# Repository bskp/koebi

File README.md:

Köbi: Robotic Puppeteering
==========================

Köbi is a 6-channel wireless stepper controller consisting of a [SparkFun ESP32 Thing](https://www.sparkfun.com/products/13907) (red) and a **breakout shield** (white). The latter is inspired by [RAMPS](https://reprap.org/wiki/Arduino_Mega_Pololu_Shield) and accomodates six stepper motor drivers ([TMC2130 StepSticks](https://shop.watterott.com/SilentStepStick-TMC2130), green), optical endstop sensors and fan control.

The software on the ESP32 provides an [OSC (Open Sound Control)](https://en.wikipedia.org/wiki/Open_Sound_Control) server. This, in combination with a matching tablet GUI for the modular [TouchOSC](https://hexler.net/products/touchosc) app allows easy control of the steppers (which are the six thread spools).

Alternatively, the module can be controlled by any other OSC client. The OSC endpoints are documented at the [end of this page](#osc-api).

Features
--------

- 500g per thread
- Velocities up to 2m/s
- Wireless control
- Sub-centimeter precision
- (Almost) unlimited thread lengths
- Position and speed feedback for every channel
- Self-calibration using optical markers on the threads (TODO)
- Motor drivers configured using SPI, allowing for:
    - Microstepping reconfiguration (during operation)
    - Current control
    - Load estimation (TODO)
    - Count of missed steps if overload occurs (TODO)
- Easily extendable code written in [Micropython](https://micropython.org)
- Wireless console (WEBREPL) and code update (FTP)
- Additional I2C / SPI / GPIOs broken out

There are a ton of things you can hook it to. Feel free to reuse!

Software + Firmware
-------------------

The ESP32-Board runs a **special build** of the Micropython firmware due to two requirements:

- The PWM hardware module, which generates the **pulses for the  stepper motors**, is currently not supported by Micropython. This special build includes a Python module supporting it, implemented in C: The [MCPWM](https://github.com/bskp/micropython_esp32_mcpwm) module.

- The Python module for the **Trinamic TMC steppper drivers** (which holds names and descriptions to dozens of its registers) had to be frozen in order to save memory: The [TMC]() module. (TODO: Not published yet)

How much do you need? To get you started with the software, each of this three guides covers a different level:
1. **[Getting started](getting_started.md)**: Setup and interact with Köbi _using a tablet_ and the default OSC API
2. **[Hacking](hacking.md)**: Extend Köbis functionality _by modifying the Micropython_ code running the ESP32
3. **[Developing](developing.md)**: Modify the _Micropython firmware (written in C)_ to improve on the modules [MCPWM]() or [TMC](). These are part of the modified Micropython built, ie. "frozen"

Hardware
--------

This repo also supplies you with everything needed to build your own Köbi.

### Bill of Ordering Materials

| Thing                 | Brand    | Part      | Source          | Price |
|-----------------------|----------|-----------|-----------------|-------|
| Steppers (5-pack)     | Hanpose  | 17HS4401  | AliExpress      | 38.-  |
| Voltage Supply (120W) | GYU&PW   | S-120-24  | AliExpress      | 13.-  |
| ESP32 Thing           | SparkFun | DEV-13907 | [bastelgarage](https://www.bastelgarage.ch/sparkfun-esp32-thing) | 22.- |

SN74LS138N

- bom: steppers, supply, esp32, tmcs, pcb/components, wall plug

### 3D Printed Parts

**Thread Spool (40mm)**: [.stl](parts/Sp40A.stl)

- stl, link zu onshape

### Printed Circuit Board
- PCB-Daten als pdf, gerber und kicad.

Ideas
-----

- [x] Coordinated 2-axis movements
- [ ] Load visualization
- [ ] Presets with persistent storage
- [ ] Self-calibration with markers
- [x] Sequencer (Sine and jitter movements)
- [x] Coordinated movements for more than 2 axes
- [ ] Inverse kinematics

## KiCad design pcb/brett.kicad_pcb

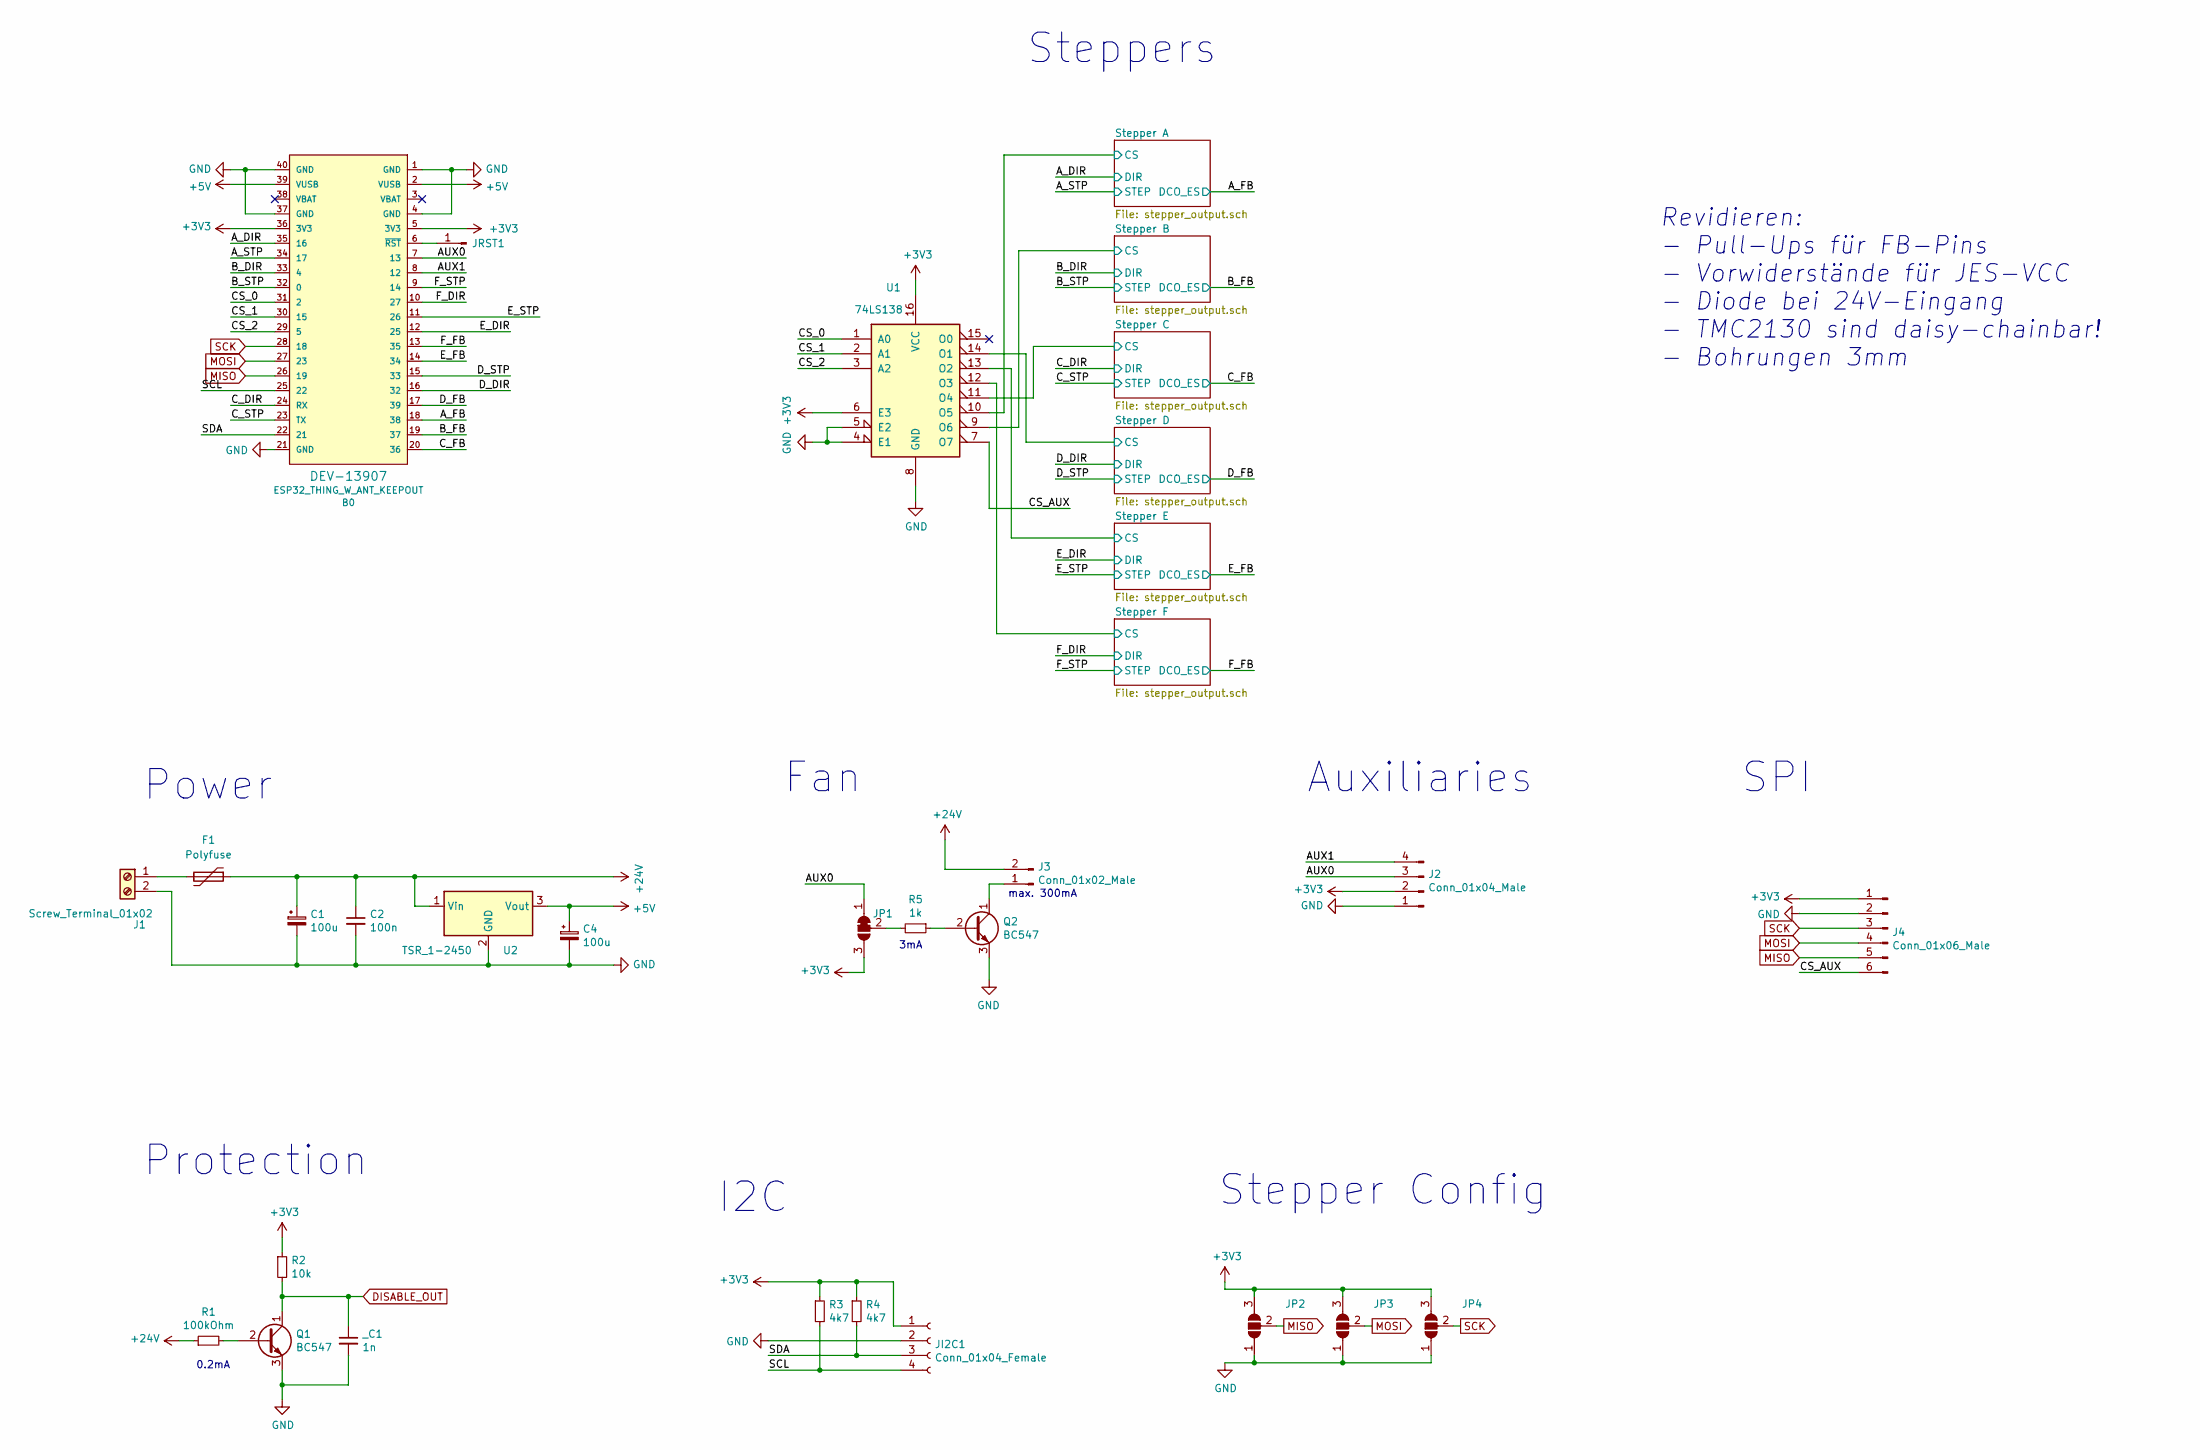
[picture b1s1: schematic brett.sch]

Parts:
B0: ESP32_THING_W_ANT_KEEPOUT; ESP32_THING
C1, C4: 100u; CP_Radial_D8.0mm_P3.50mm
C2: 100n; C_Radial_D6.3mm_H5.0mm_P2.50mm
F1: Polyfuse; Fuse_Bourns_MF-RHT1000
J1: Screw_Terminal_01x02; TerminalBlock_RND_205-00232_1x02_P5.08mm_Horizontal
J2: Conn_01x04_Male; PinHeader_1x04_P2.54mm_Vertical
J3: Conn_01x02_Male; PinHeader_1x02_P2.54mm_Vertical
J4: Conn_01x06_Male; PinHeader_1x06_P2.54mm_Vertical
JI2C1: Conn_01x04_Female; PinHeader_1x04_P2.54mm_Vertical
JP1: SolderJumper_3_Bridged12; SolderJumper-3_P1.3mm_Bridged12_RoundedPad1.0x1.5mm
JP2, JP3, JP4: SolderJumper_3_Open; SolderJumper-3_P1.3mm_Open_RoundedPad1.0x1.5mm
JRST1: Conn_01x01_Male; PinHeader_1x01_P2.54mm_Vertical
Q1, Q2: BC547; TO-92_Inline
R1: 100kOhm; R_Axial_DIN0207_L6.3mm_D2.5mm_P7.62mm_Horizontal
R2: 10k; R_Axial_DIN0207_L6.3mm_D2.5mm_P7.62mm_Horizontal
R3, R4: 4k7; R_Axial_DIN0207_L6.3mm_D2.5mm_P7.62mm_Horizontal
R5: 1k; R_Axial_DIN0207_L6.3mm_D2.5mm_P7.62mm_Horizontal
U1: 74LS138; DIP-16_W7.62mm
U2: TSR_1-2450; Converter_DCDC_TRACO_TSR-1_THT
_C1: 1n; C_Radial_D6.3mm_H5.0mm_P2.50mm

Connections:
+5V: B0.2 (VUSB), B0.39 (VUSB), C4.1, U2.3 (Vout)
+24V: C1.1, C2.1, F1.1, J3.2, R1.1, U2.1 (Vin); also elsewhere on the board
/AUX0: B0.7 (13), J2.3, JP1.1 (A); also elsewhere on the board
/AUX1: B0.8 (12), J2.4; also elsewhere on the board
/A_DIR: B0.35 (16); also elsewhere on the board
/A_FB: B0.18 (38); also elsewhere on the board
/A_STP: B0.34 (17); also elsewhere on the board
/B_DIR: B0.33 (4); also elsewhere on the board
/B_FB: B0.19 (37); also elsewhere on the board
/B_STP: B0.32 (0); also elsewhere on the board
/CS_0: B0.31 (2), U1.1 (A0)
/CS_1: B0.30 (15), U1.2 (A1)
/CS_2: B0.29 (5), U1.3 (A2)
/CS_AUX: J4.6, U1.7 (O7); also elsewhere on the board
/C_DIR: B0.24 (RX); also elsewhere on the board
/C_FB: B0.20 (36); also elsewhere on the board
/C_STP: B0.23 (TX); also elsewhere on the board
/D_DIR: B0.16 (32); also elsewhere on the board
/D_FB: B0.17 (39); also elsewhere on the board
/D_STP: B0.15 (33); also elsewhere on the board
/E_DIR: B0.12 (25); also elsewhere on the board
/E_FB: B0.14 (34); also elsewhere on the board
/E_STP: B0.11 (26); also elsewhere on the board
/F_DIR: B0.10 (27); also elsewhere on the board
/F_FB: B0.13 (35); also elsewhere on the board
/F_STP: B0.9 (14); also elsewhere on the board
/SCL: B0.25 (22), JI2C1.4, R3.2
/SDA: B0.22 (21), JI2C1.3, R4.2
/Stepper A/CS: U1.10 (O5); also elsewhere on the board
/Stepper B/CS: U1.9 (O6); also elsewhere on the board
/Stepper C/CS: U1.11 (O4); also elsewhere on the board
/Stepper D/CS: U1.14 (O1); also elsewhere on the board
/Stepper E/CS: U1.13 (O2); also elsewhere on the board
/Stepper F/CS: U1.12 (O3); also elsewhere on the board
DISABLE_OUT: Q1.1 (C), R2.2, _C1.1; also elsewhere on the board
MISO: B0.26 (19), J4.5, JP2.2 (C); also elsewhere on the board
MOSI: B0.27 (23), J4.4, JP3.2 (C); also elsewhere on the board
unnamed: B0.6 (~RST~), JRST1.1
unnamed: F1.2, J1.1
unnamed: J3.1, Q2.1 (C)
unnamed: JP1.2 (C), R5.2
unnamed: Q1.2 (B), R1.2
unnamed: Q2.2 (B), R5.1
SCK: B0.28 (18), J4.3, JP4.2 (C); also elsewhere on the board

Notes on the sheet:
Stepper Config
Power
I2C
Protection
Fan
3mA
max. 300mA
Auxiliaries
0.2mA
Steppers
SPI
Revidieren: - Pull-Ups für FB-Pins - Vorwiderstände für JES-VCC - Diode bei 24V-Eingang - TMC2130 sind daisy-chainbar! - Bohrungen 3mm

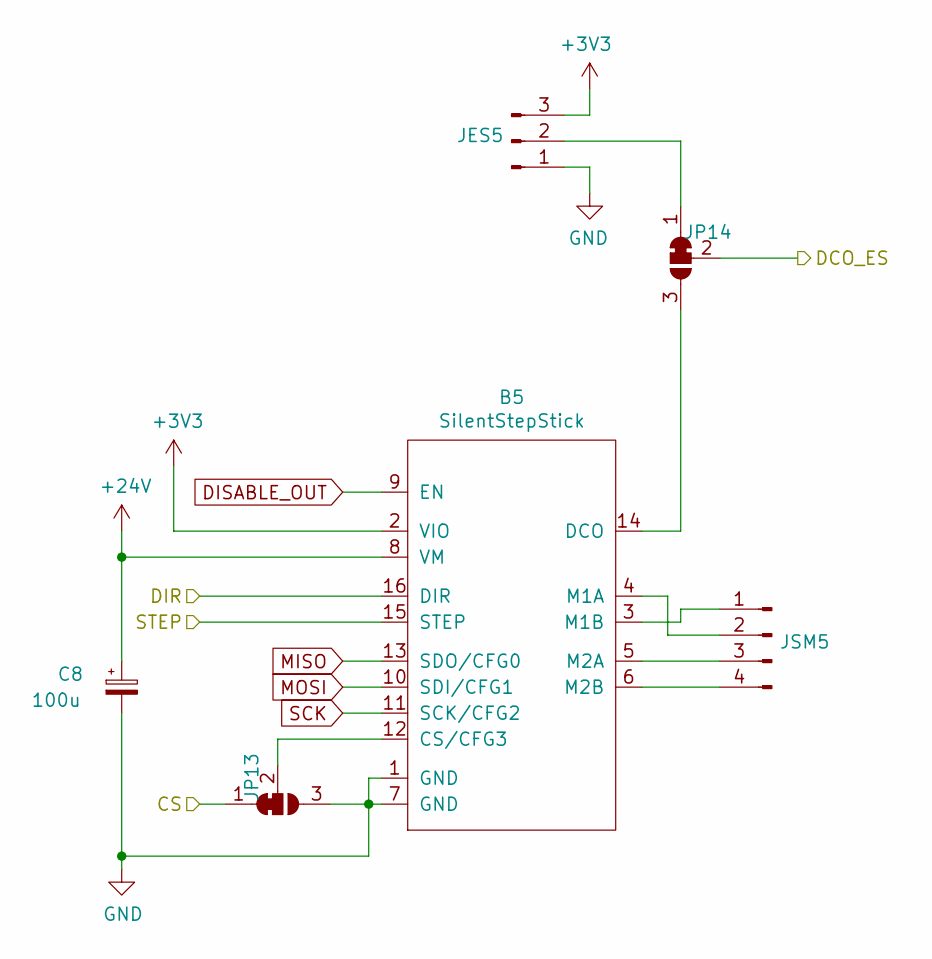
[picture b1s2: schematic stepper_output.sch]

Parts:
B1: SilentStepStick; StepStick
C3: 100u; CP_Radial_D8.0mm_P3.50mm
JES1: Conn_01x03_Male; PinHeader_1x03_P2.54mm_Vertical
JP8, JP9: SolderJumper_3_Bridged12; SolderJumper-3_P1.3mm_Bridged12_RoundedPad1.0x1.5mm
JSM1: Conn_01x04_Male; PinHeader_1x04_P2.54mm_Vertical

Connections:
+24V: B1.8 (VM), C3.1; also elsewhere on the board
/A_DIR: B1.16 (DIR); also elsewhere on the board
/A_FB: JP9.2 (C); also elsewhere on the board
/A_STP: B1.15 (STEP); also elsewhere on the board
/Stepper A/CS: JP8.1 (A); also elsewhere on the board
DISABLE_OUT: B1.9 (EN); also elsewhere on the board
MISO: B1.13 (SDO/CFG0); also elsewhere on the board
MOSI: B1.10 (SDI/CFG1); also elsewhere on the board
unnamed: B1.3 (M1B), JSM1.1
unnamed: B1.4 (M1A), JSM1.2
unnamed: B1.5 (M2A), JSM1.3
unnamed: B1.6 (M2B), JSM1.4
unnamed: B1.12 (CS/CFG3), JP8.2 (C)
unnamed: B1.14 (DCO), JP9.3 (B)
unnamed: JES1.2, JP9.1 (A)
SCK: B1.11 (SCK/CFG2); also elsewhere on the board

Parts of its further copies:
B2, B3, B4, B5, B6: SilentStepStick; StepStick
C5, C6, C7, C8, C9: 100u; CP_Radial_D8.0mm_P3.50mm
J5: Conn_01x03_Male; PinHeader_1x03_P2.54mm_Vertical
J6: Conn_01x04_Male; PinHeader_1x04_P2.54mm_Vertical
JES2, JES3, JES4, JES5, JES6: Conn_01x03_Male; PinHeader_1x03_P2.54mm_Vertical
JP5, JP6, JP7, JP10, JP11, JP12, JP13, JP14, JP15, JP16: SolderJumper_3_Bridged12; SolderJumper-3_P1.3mm_Bridged12_RoundedPad1.0x1.5mm
JSM2, JSM3, JSM4, JSM5, JSM6: Conn_01x04_Male; PinHeader_1x04_P2.54mm_Vertical

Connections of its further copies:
+24V: B2.8 (VM), B3.8 (VM), B4.8 (VM), B5.8 (VM), B6.8 (VM), C5.1, C6.1, C7.1, C8.1, C9.1; also elsewhere on the board
/B_DIR: B2.16 (DIR); also elsewhere on the board
/B_FB: JP6.2 (C); also elsewhere on the board
/B_STP: B2.15 (STEP); also elsewhere on the board
/C_DIR: B3.16 (DIR); also elsewhere on the board
/C_FB: JP10.2 (C); also elsewhere on the board
/C_STP: B3.15 (STEP); also elsewhere on the board
/D_DIR: B4.16 (DIR); also elsewhere on the board
/D_FB: JP12.2 (C); also elsewhere on the board
/D_STP: B4.15 (STEP); also elsewhere on the board
/E_DIR: B5.16 (DIR); also elsewhere on the board
/E_FB: JP14.2 (C); also elsewhere on the board
/E_STP: B5.15 (STEP); also elsewhere on the board
/F_DIR: B6.16 (DIR); also elsewhere on the board
/F_FB: JP16.2 (C); also elsewhere on the board
/F_STP: B6.15 (STEP); also elsewhere on the board
/Stepper B/CS: JP5.1 (A); also elsewhere on the board
/Stepper C/CS: JP7.1 (A); also elsewhere on the board
/Stepper D/CS: JP11.1 (A); also elsewhere on the board
/Stepper E/CS: JP13.1 (A); also elsewhere on the board
/Stepper F/CS: JP15.1 (A); also elsewhere on the board
DISABLE_OUT: B2.9 (EN), B3.9 (EN), B4.9 (EN), B5.9 (EN), B6.9 (EN); also elsewhere on the board
MISO: B2.13 (SDO/CFG0), B3.13 (SDO/CFG0), B4.13 (SDO/CFG0), B5.13 (SDO/CFG0), B6.13 (SDO/CFG0); also elsewhere on the board
MOSI: B2.10 (SDI/CFG1), B3.10 (SDI/CFG1), B4.10 (SDI/CFG1), B5.10 (SDI/CFG1), B6.10 (SDI/CFG1); also elsewhere on the board
unnamed: B2.3 (M1B), JSM2.1
unnamed: B2.4 (M1A), JSM2.2
unnamed: B2.5 (M2A), JSM2.3
unnamed: B2.6 (M2B), JSM2.4
unnamed: B2.12 (CS/CFG3), JP5.2 (C)
unnamed: B2.14 (DCO), JP6.3 (B)
unnamed: B3.3 (M1B), JSM3.1
unnamed: B3.4 (M1A), JSM3.2
unnamed: B3.5 (M2A), JSM3.3
unnamed: B3.6 (M2B), JSM3.4
unnamed: B3.12 (CS/CFG3), JP7.2 (C)
unnamed: B3.14 (DCO), JP10.3 (B)
unnamed: B4.3 (M1B), JSM4.1
unnamed: B4.4 (M1A), JSM4.2
unnamed: B4.5 (M2A), JSM4.3
unnamed: B4.6 (M2B), JSM4.4
unnamed: B4.12 (CS/CFG3), JP11.2 (C)
unnamed: B4.14 (DCO), JP12.3 (B)
unnamed: B5.3 (M1B), JSM5.1
unnamed: B5.4 (M1A), JSM5.2
unnamed: B5.5 (M2A), JSM5.3
unnamed: B5.6 (M2B), JSM5.4
unnamed: B5.12 (CS/CFG3), JP13.2 (C)
unnamed: B5.14 (DCO), JP14.3 (B)
unnamed: B6.3 (M1B), JSM6.1
unnamed: B6.4 (M1A), JSM6.2
unnamed: B6.5 (M2A), JSM6.3
unnamed: B6.6 (M2B), JSM6.4
unnamed: B6.12 (CS/CFG3), JP15.2 (C)
unnamed: B6.14 (DCO), JP16.3 (B)
unnamed: JES2.2, JP6.1 (A)
unnamed: JES3.2, JP10.1 (A)
unnamed: JES4.2, JP12.1 (A)
unnamed: JES5.2, JP14.1 (A)
unnamed: JES6.2, JP16.1 (A)
SCK: B2.11 (SCK/CFG2), B3.11 (SCK/CFG2), B4.11 (SCK/CFG2), B5.11 (SCK/CFG2), B6.11 (SCK/CFG2); also elsewhere on the board

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
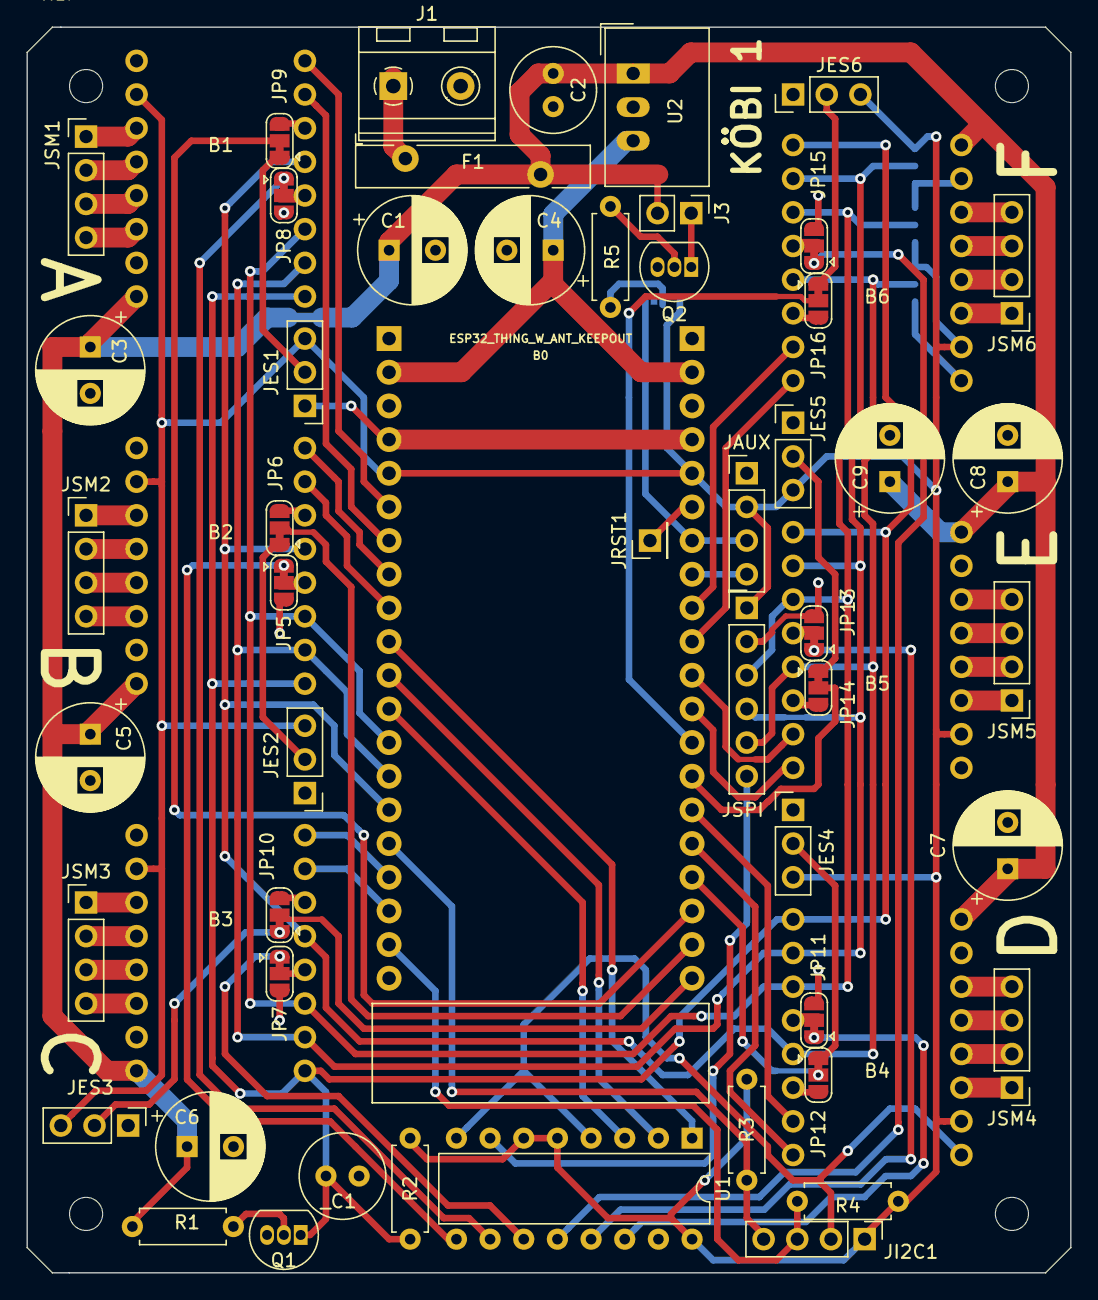
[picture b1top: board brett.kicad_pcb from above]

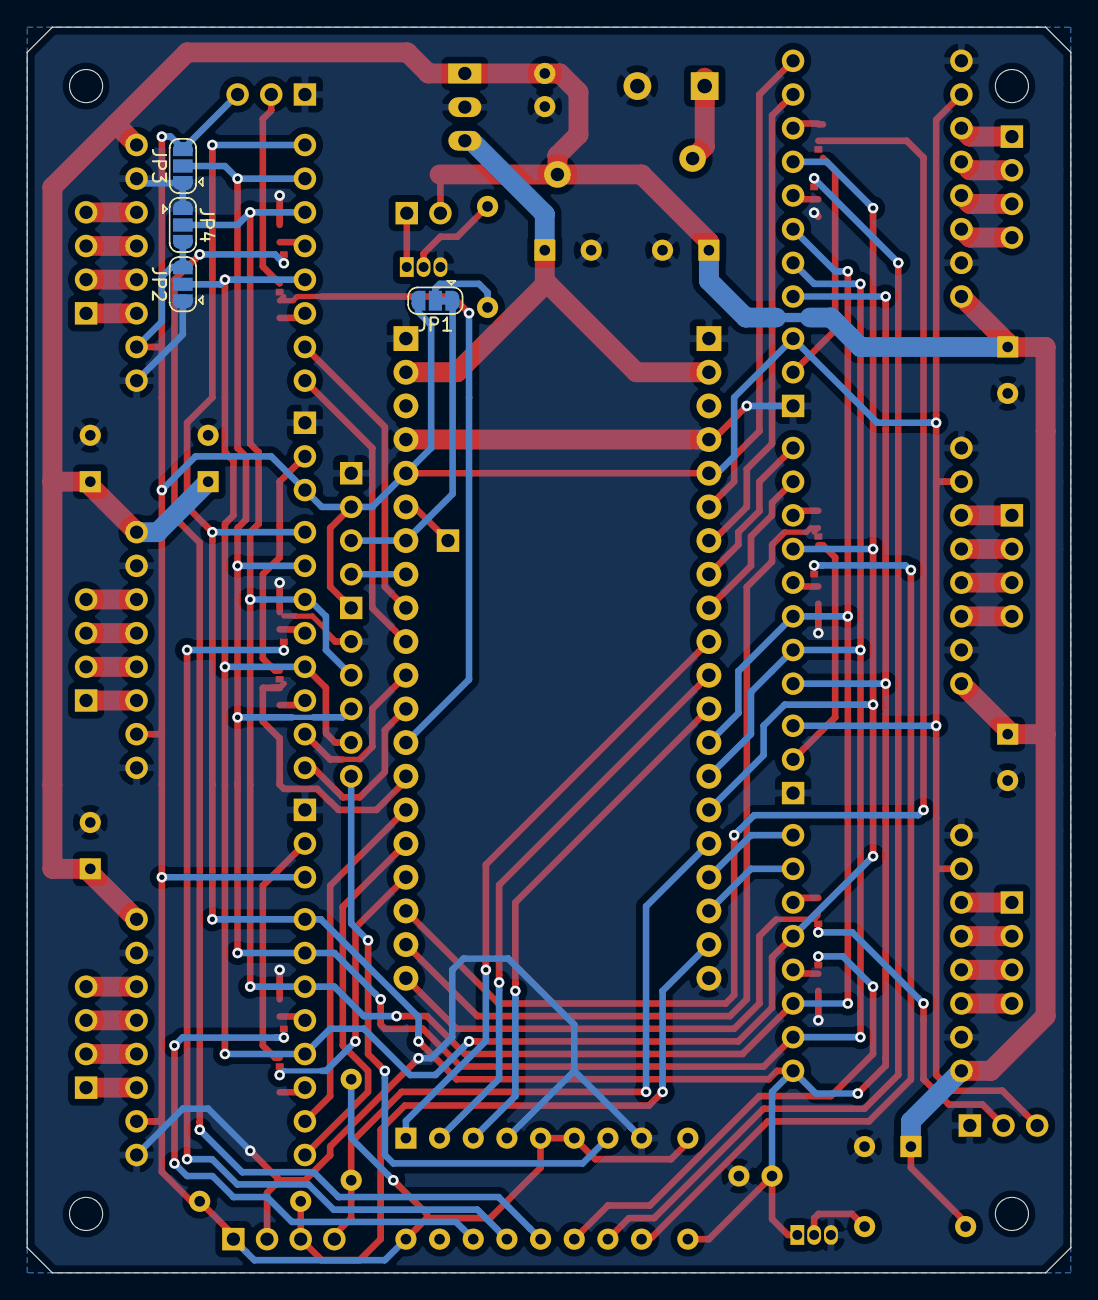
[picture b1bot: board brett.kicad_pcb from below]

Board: 2 copper layers, 78.7 x 94.0 mm, 61 parts (4 on the bottom side), 88 nets.

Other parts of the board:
JAUX: Conn_01x04_Male; PinHeader_1x04_P2.54mm_Vertical
JSPI: Conn_01x06_Male; PinHeader_1x06_P2.54mm_Vertical

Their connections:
/AUX0: JAUX.3; also elsewhere on the board
/AUX1: JAUX.4; also elsewhere on the board
/CS_AUX: JSPI.6; also elsewhere on the board
MISO: JSPI.5; also elsewhere on the board
MOSI: JSPI.4; also elsewhere on the board
SCK: JSPI.3; also elsewhere on the board

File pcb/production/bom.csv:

"ID";"Bezeichner";"Gehäuse";"Stückzahl";"Bezeichnung";"Anbieter und Referenz";
1;"REF**,REF**,REF**,REF**";"MountingHole_2.5mm";4;"MountingHole_2.5mm";;;
2;"JSPI";"PinHeader_1x06_P2.54mm_Vertical";1;"Conn_01x06_Male";;;
3;"JAUX,JSM2,JSM6,JSM5,JSM4,JSM3,JSM1";"PinHeader_1x04_P2.54mm_Vertical";7;"Conn_01x04_Male";;;
4;"B0";"ESP32_THING";1;"ESP32_THING_W_ANT_KEEPOUT";;;
5;"U1";"DIP-16_W7.62mm";1;"74LS138";;;
6;"B6,B5,B4,B3,B2,B1";"StepStick";6;"SilentStepStick";;;
7;"JP6,JP5,JP16,JP15,JP14,JP13,JP12,JP11,JP10,JP7,JP9,JP8,JP1";"SolderJumper-3_P1.3mm_Bridged12_RoundedPad1.0x1.5mm";13;"SolderJumper_3_Bridged12";;;
8;"JES2,JES6,JES5,JES4,JES3,JES1";"PinHeader_1x03_P2.54mm_Vertical";6;"Conn_01x03_Male";;;
9;"C5,C9,C8,C7,C6,C3,C4,C1";"CP_Radial_D8.0mm_P3.50mm";8;"100u";;;
10;"JRST1";"PinHeader_1x01_P2.54mm_Vertical";1;"Conn_01x01_Male";;;
11;"_C1";"C_Radial_D6.3mm_H5.0mm_P2.50mm";1;"1n";;;
12;"U2";"Converter_DCDC_TRACO_TSR-1_THT";1;"TSR_1-2450";;;
13;"R5";"R_Axial_DIN0207_L6.3mm_D2.5mm_P7.62mm_Horizontal";1;"1k";;;
14;"R4,R3";"R_Axial_DIN0207_L6.3mm_D2.5mm_P7.62mm_Horizontal";2;"4k7";;;
15;"R2";"R_Axial_DIN0207_L6.3mm_D2.5mm_P7.62mm_Horizontal";1;"10k";;;
16;"R1";"R_Axial_DIN0207_L6.3mm_D2.5mm_P7.62mm_Horizontal";1;"100kOhm";;;
17;"Q2,Q1";"TO-92_Inline";2;"BC547";;;
18;"JP4,JP3,JP2";"SolderJumper-3_P1.3mm_Open_RoundedPad1.0x1.5mm";3;"SolderJumper_3_Open";;;
19;"J3";"PinHeader_1x02_P2.54mm_Vertical";1;"Conn_01x02_Male";;;
20;"JI2C1";"PinHeader_1x04_P2.54mm_Vertical";1;"Conn_01x04_Female";;;
21;"J1";"TerminalBlock_RND_205-00232_1x02_P5.08mm_Horizontal";1;"Screw_Terminal_01x02";;;
22;"F1";"Fuse_Bourns_MF-RHT1000";1;"Polyfuse";;;
23;"C2";"C_Radial_D6.3mm_H5.0mm_P2.50mm";1;"100n";;;

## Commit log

2019-12-16 Initial commit.
2019-12-16 Partial GUI updates, higher rate.
2019-12-17 Consistent naming in remote.py
2019-12-17 Performance optimization on gui_update
2019-12-17 Stable operation (removed perf logging)
2019-12-19 added uftp
2019-12-29 Updated README, proper esp/micropython versions
2019-12-29 Readme update, added MIT License
2020-03-29 Bumped Submodules, new docs
